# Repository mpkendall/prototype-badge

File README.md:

# prototype-badge
pcb badges for prototype!

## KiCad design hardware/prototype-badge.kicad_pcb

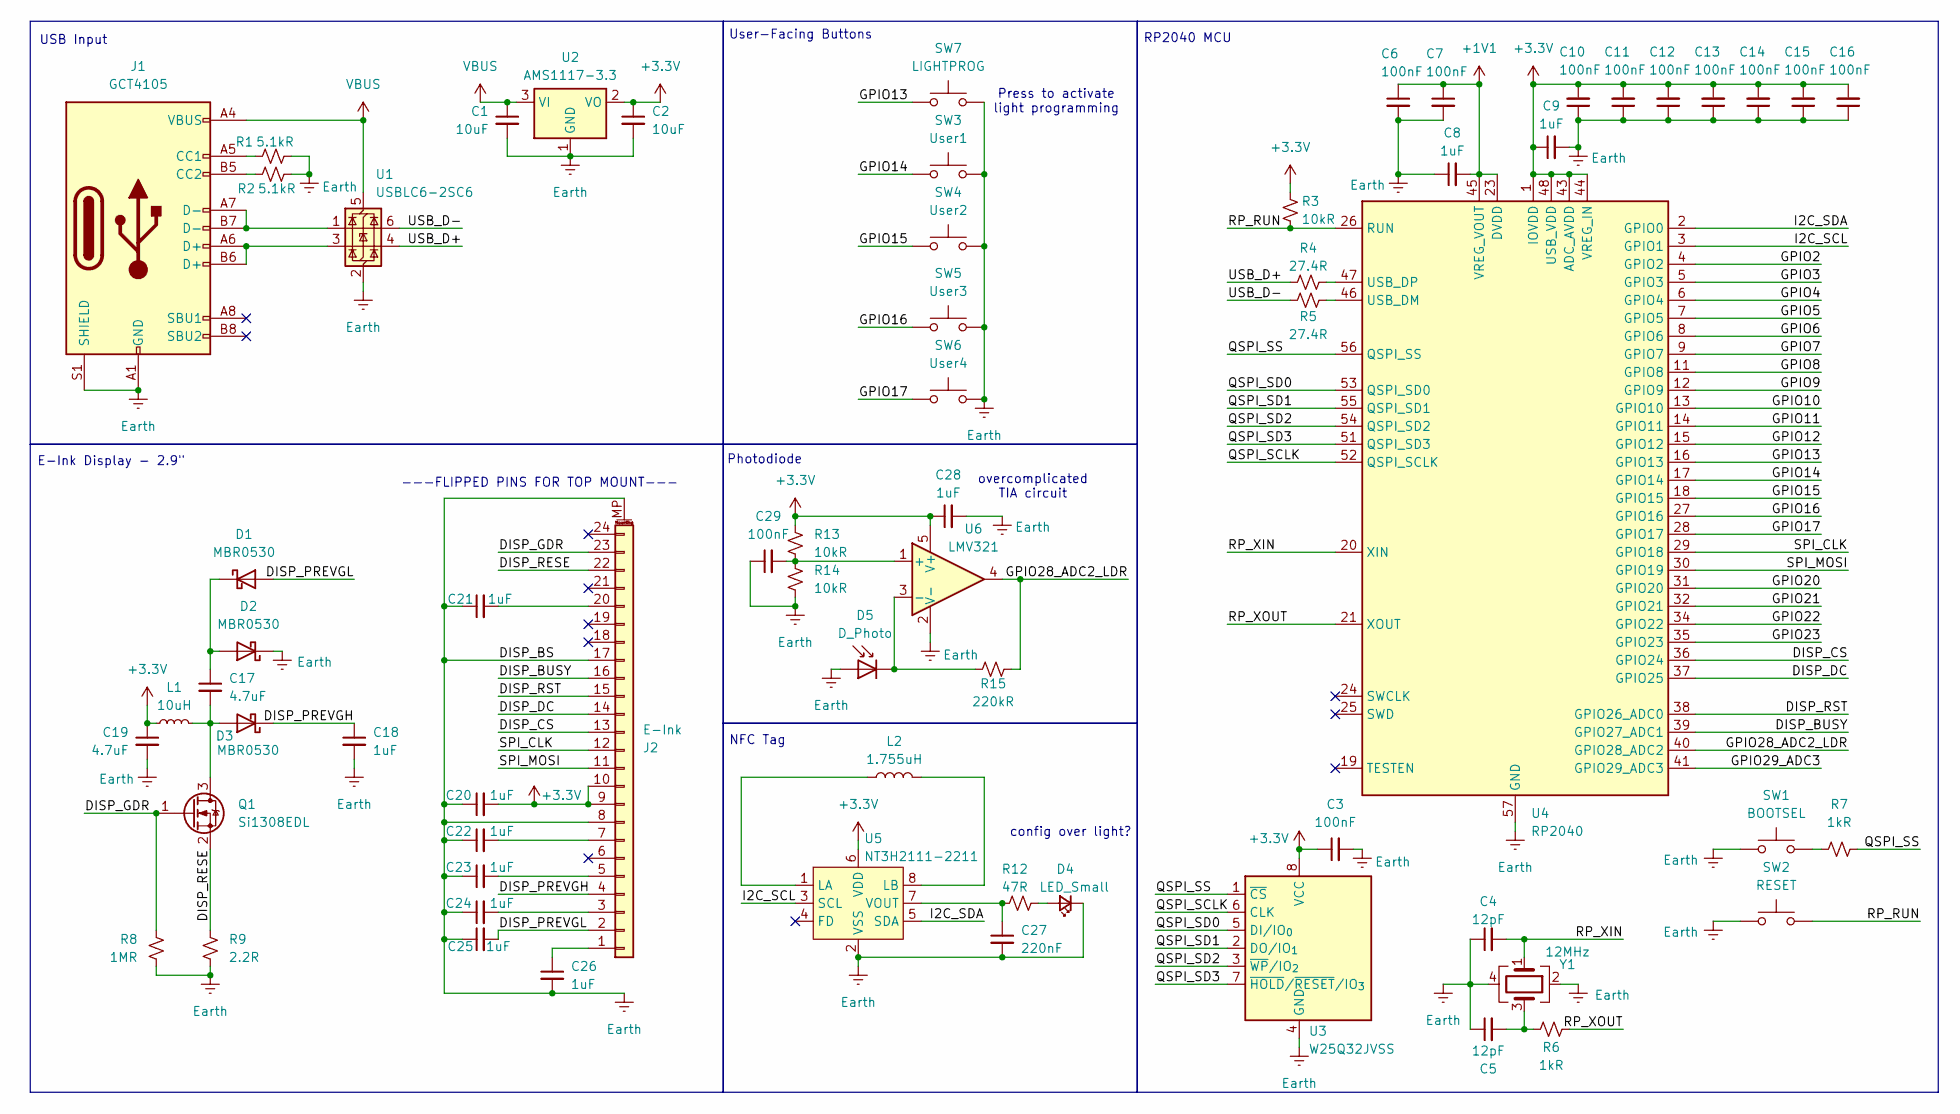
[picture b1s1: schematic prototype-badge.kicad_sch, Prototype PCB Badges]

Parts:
C1, C2: 10uF; C_0603_1608Metric; LCSC C19702
C3, C6, C7, C10, C11, C12, C13, C14, C15, C16, C29: 100nF; C_0402_1005Metric; LCSC C1525
C4, C5: 12pF; C_0402_1005Metric; LCSC C1547
C8, C9, C18, C20, C21, C22, C23, C24, C25, C26, C28: 1uF; C_0603_1608Metric; LCSC C15849
C17, C19: 4.7uF; C_0603_1608Metric; LCSC C69335
C27: 220nF; C_0402_1005Metric; LCSC C16772
D1, D2, D3: MBR0530; D_SOD-123; LCSC C82046
D4: LED_Small; LED_0603_1608Metric; LCSC C2286
D5: D_Photo; Kingbright_KPS-3227; LCSC C2689207
J1: GCT4105; USB_C_Receptacle_GCT_USB4105-xx-A_16P_TopMnt_Horizontal; LCSC C2760486
J2: E-Ink; TE_2-1734839-4_1x24-1MP_P0.5mm_Horizontal; LCSC C5362165
L1: 10uH; L_APV_ANR4018; LCSC C167808
L2: 1.755uH; nfc-coil-2
Q1: Si1308EDL; SOT-323_SC-70; LCSC C7603347
R1, R2: 5.1kR; R_0402_1005Metric; LCSC C25905
R3, R13, R14: 10kR; R_0402_1005Metric; LCSC C25744
R4, R5: 27.4R; R_0402_1005Metric; LCSC C274349
R6, R7: 1kR; R_0402_1005Metric; LCSC C11702
R8: 1MR; R_0603_1608Metric; LCSC C22935
R9: 2.2R; R_0603_1608Metric; LCSC C22939
R12: 47R; R_0603_1608Metric; LCSC C23182
R15: 220kR; R_0603_1608Metric; LCSC C22961
SW1: BOOTSEL; SW_Tactile_SPST_NO_Straight_CK_PTS636Sx25SMTRLFS; LCSC C318938
SW2: RESET; SW_Tactile_SPST_NO_Straight_CK_PTS636Sx25SMTRLFS; LCSC C318938
SW3: User1; SW_Tactile_SPST_NO_Straight_CK_PTS636Sx25SMTRLFS; LCSC C318938
SW4: User2; SW_Tactile_SPST_NO_Straight_CK_PTS636Sx25SMTRLFS; LCSC C318938
SW5: User3; SW_Tactile_SPST_NO_Straight_CK_PTS636Sx25SMTRLFS; LCSC C318938
SW6: User4; SW_Tactile_SPST_NO_Straight_CK_PTS636Sx25SMTRLFS; LCSC C318938
SW7: LIGHTPROG; SW_Tactile_SPST_NO_Straight_CK_PTS636Sx25SMTRLFS; LCSC C318938
U1: USBLC6-2SC6; SOT-23-6; LCSC C7519
U2: AMS1117-3.3; SOT-223-3_TabPin2; LCSC C18906017
U3: W25Q32JVSS; SOIC-8_5.3x5.3mm_P1.27mm; LCSC C97521
U4: RP2040; QFN-56-1EP_7x7mm_P0.4mm_EP3.2x3.2mm; LCSC C2040
U5: NT3H2111-2211; NT3H2111W0FHKH; LCSC C710403
U6: LMV321; SOT-23-5; LCSC C7972
Y1: 12MHz; Crystal_SMD_3225-4Pin_3.2x2.5mm; LCSC C37635368

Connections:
+1V1: C6.1, C7.1, C8.2, U4.23 (DVDD), U4.45 (VREG_VOUT), U4.50 (DVDD)
+3.3V: C2.1, C3.1, C9.1, C10.2, C11.2, C12.2, C13.2, C14.2, C15.2, C16.2, C19.1, C20.2, C28.1, J2.9, J2.10, L1.1, R3.1, R13.1, U2.2 (VO), U3.8 (VCC), U4.1 (IOVDD), U4.10 (IOVDD), U4.22 (IOVDD), U4.33 (IOVDD), U4.42 (IOVDD), U4.43 (ADC_AVDD), U4.44 (VREG_IN), U4.48 (USB_VDD), U4.49 (IOVDD), U5.6 (VDD), U6.5 (V+)
/DISP_BUSY: J2.16, U4.39 (GPIO27_ADC1)
/DISP_CS: J2.13, U4.36 (GPIO24)
/DISP_DC: J2.14, U4.37 (GPIO25)
/DISP_GDR: J2.23, Q1.1 (G), R8.2
/DISP_PREVGH: C18.1, D3.1 (K), J2.4
/DISP_PREVGL: C25.2, D1.2 (A), J2.2
/DISP_RESE: J2.22, Q1.2 (S), R9.1
/DISP_RST: J2.15, U4.38 (GPIO26_ADC0)
/GPIO2: U4.4 (GPIO2)
/GPIO3: U4.5 (GPIO3)
/GPIO4: U4.6 (GPIO4)
/GPIO5: U4.7 (GPIO5)
/GPIO6: U4.8 (GPIO6)
/GPIO7: U4.9 (GPIO7)
/GPIO8: U4.11 (GPIO8)
/GPIO9: U4.12 (GPIO9)
/GPIO10: U4.13 (GPIO10)
/GPIO11: U4.14 (GPIO11)
/GPIO12: U4.15 (GPIO12)
/GPIO13: SW7.1, U4.16 (GPIO13)
/GPIO14: SW3.1, U4.17 (GPIO14)
/GPIO15: SW4.1, U4.18 (GPIO15)
/GPIO16: SW5.1, U4.27 (GPIO16)
/GPIO17: SW6.1, U4.28 (GPIO17)
/GPIO20: U4.31 (GPIO20)
/GPIO21: U4.32 (GPIO21)
/GPIO22: U4.34 (GPIO22)
/GPIO23: U4.35 (GPIO23)
/GPIO28_ADC2_LDR: R15.1, U4.40 (GPIO28_ADC2), U6.4
/GPIO29_ADC3: U4.41 (GPIO29_ADC3)
/I2C_SCL: U4.3 (GPIO1), U5.3 (SCL)
/I2C_SDA: U4.2 (GPIO0), U5.5 (SDA)
/QSPI_SCLK: U3.6 (CLK), U4.52 (QSPI_SCLK)
/QSPI_SD0: U3.5 (DI/IO_{0}), U4.53 (QSPI_SD0)
/QSPI_SD1: U3.2 (DO/IO_{1}), U4.55 (QSPI_SD1)
/QSPI_SD2: U3.3 (~WP/IO_{2}), U4.54 (QSPI_SD2)
/QSPI_SD3: U3.7 (~HOLD/~RESET/IO_{3}), U4.51 (QSPI_SD3)
/QSPI_SS: R7.2, U3.1 (~CS), U4.56 (QSPI_SS)
/RP_RUN: R3.2, SW2.2, U4.26 (RUN)
/RP_XIN: C4.2, U4.20 (XIN), Y1.1
/RP_XOUT: R6.1, U4.21 (XOUT)
/SPI_CLK: J2.12, U4.29 (GPIO18)
/SPI_MOSI: J2.11, U4.30 (GPIO19)
/USB_D+: R4.1, U1.4 (I/O2)
/USB_D-: R5.2, U1.6 (I/O1)
Earth: C1.2, C2.2, C3.2, C4.1, C5.1, C6.2, C7.2, C8.1, C9.2, C10.1, C11.1, C12.1, C13.1, C14.1, C15.1, C16.1, C18.2, C19.2, C20.1, C21.1, C22.1, C23.1, C24.1, C25.1, C26.2, C27.2, C28.2, C29.1, D2.1 (K), D4.1 (K), D5.2 (A), J1.A1 (GND), J1.A12 (GND), J1.B1 (GND), J1.B12 (GND), J1.S1 (SHIELD), J2.8, J2.17, J2.MP (MountPin), R1.1, R2.2, R8.1, R9.2, R14.2, SW1.1, SW2.1, SW3.2, SW4.2, SW5.2, SW6.2, SW7.2, U1.2 (GND), U2.1 (GND), U3.4 (GND), U4.57 (GND), U5.2 (VSS), U6.2 (V-), Y1.2, Y1.4
unnamed: C5.2, R6.2, Y1.3
unnamed: C17.1, D1.1 (K), D2.2 (A)
unnamed: C17.2, D3.2 (A), L1.2, Q1.3 (D)
unnamed: D4.2 (A), R12.2
unnamed: D5.1 (K), R15.2, U6.3 (-)
unnamed: J1.A5 (CC1), R1.2
unnamed: J1.B5 (CC2), R2.1
unnamed: J1.A6 (D+), J1.B6 (D+), U1.3 (I/O2)
unnamed: J1.A7 (D-), J1.B7 (D-), U1.1 (I/O1)
unnamed: C26.1, J2.1
unnamed: C24.2, J2.3
unnamed: C23.2, J2.5
unnamed: C22.2, J2.7
unnamed: C21.2, J2.20
unnamed: R7.1, SW1.2
unnamed: R5.1, U4.46 (USB_DM)
unnamed: R4.2, U4.47 (USB_DP)
unnamed: L2.1, U5.1 (LA)
unnamed: L2.2, U5.8 (LB)
unnamed: C27.1, R12.1, U5.7 (VOUT)
unnamed: C29.2, R13.2, R14.1, U6.1 (+)
VBUS: C1.1, J1.A4 (VBUS), J1.A9 (VBUS), J1.B4 (VBUS), J1.B9 (VBUS), U1.5 (VBUS), U2.3 (VI)

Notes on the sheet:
User-Facing Buttons
---FLIPPED PINS FOR TOP MOUNT---
Photodiode
Press to activate light programming
E-Ink Display - 2.9"
NFC Tag
USB Input
RP2040 MCU
overcomplicated TIA circuit
config over light?

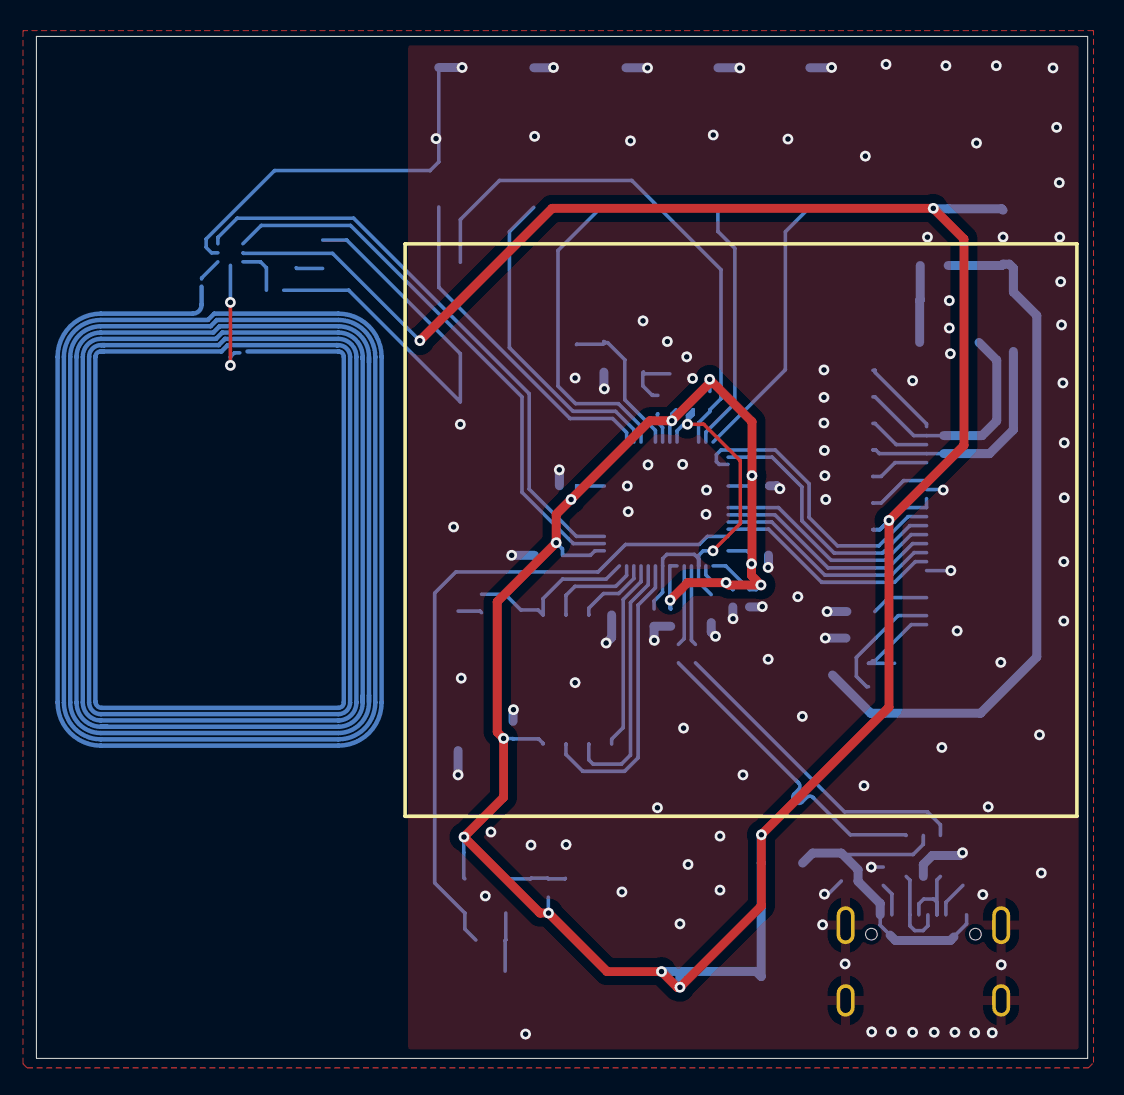
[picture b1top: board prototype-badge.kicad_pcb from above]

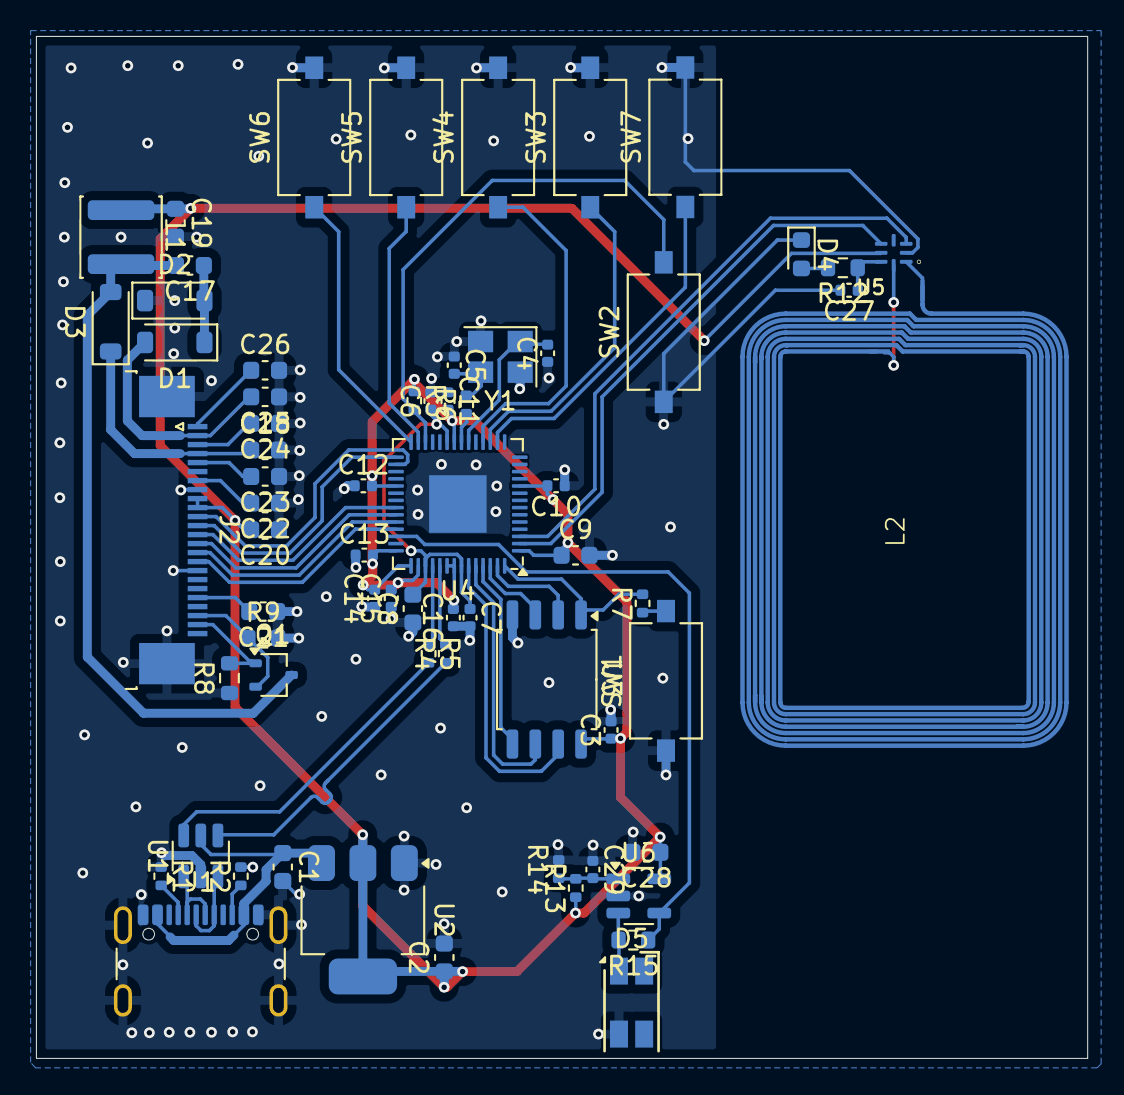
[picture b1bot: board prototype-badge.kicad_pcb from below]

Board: 2 copper layers, 58.4 x 56.8 mm, 66 parts (66 on the bottom side), 54 nets.

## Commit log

2025-11-26 base mcu schematic
2025-11-28 started pcb
2025-12-01 90% done with pcb, need to add dev pins
2025-12-02 added gpio pins - next up: finalize outline (add fpc connector + corners), add art
2025-12-03 v2 - new layout and reworked routing
2025-12-05 release candidate 1 :eyes-shaking:
2025-12-05 add a via
2025-12-05 pushing art
2025-12-05 add another via
2025-12-05 prod files!
2025-12-10 starting code + web interface
2025-12-12 more prgress with web flasher
2025-12-13 testing badge app
2025-12-13 more progress
2025-12-13 fix workflow
2025-12-13 test
2025-12-14 fixed upload hanging! dont need firmware zips anymore
2025-12-14 working badge app! still need to add photodiode stuff. config save also resets badge now
2025-12-14 bump ver number
2025-12-14 fix logging and add untested photodiode code
2025-12-14 first pass of github action
2025-12-14 try again
2025-12-14 add npm caching to workflow and streamline dependency installation
2025-12-14 add debug steps and package.json check to deployment workflow
2025-12-14 try once again
2025-12-14 i hate github actions
2025-12-14 use implicit caching
2025-12-14 use npm install
2025-12-15 test on default domain
2025-12-15 use subdomain
2025-12-15 add entry points
2025-12-15 clarify instructions
2025-12-19 it lowkey kind of works
2025-12-19 fix bug on mac
2025-12-19 tab to switch
2025-12-19 fixed merge conflict, shouldnt change anything?
2025-12-19 Added rotate method to display to fix orientation of badges
2025-12-19 updated unconfigured screen for clarity
2025-12-19 experimental nfc driver
2025-12-19 [temp] test script
2025-12-19 Enhance NFC read/write methods for improved I2C compatibility
2025-12-19 revert
2025-12-19 Rename wording
